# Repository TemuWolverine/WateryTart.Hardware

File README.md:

## [WateryTart.RaspberryPi](WateryTart.RaspberryPi/)

Raspberry Pi, a touchscreen, Hifiberry, to make a standalone amplifier/streamer that can power 30+30w speakers.
Includes 
* Fusion360 model, 
* build guide, 
* software options.

## [WateryTart.Remote](WateryTart.Remote) (work in progress)
ESP32/ESPHome based remote control to handle a household of Music Assistant devices. 

Includes
* YAML (ESPHome + HomeAssistant)
* KiCad files for custom PCB
* Gerber files for order custom PCB
* Fusion360 model

## WateryTart.Streamer (TBD)

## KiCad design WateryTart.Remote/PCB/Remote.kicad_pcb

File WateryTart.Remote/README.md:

# WateryTart.Remote
A work in progress custom remote aimed at Music Assistant devices.

## [Interactive Schematic](https://kicanvas.org/?repo=https%3A%2F%2Fgithub.com%2FTemuWolverine%2FWateryTart.Hardware%2Fblob%2Fmain%2FWateryTart.Remote%2FPCB%2FRemote.kicad_sch)
## [Interactive PCB layout](https://kicanvas.org/?repo=https%3A%2F%2Fgithub.com%2FTemuWolverine%2FWateryTart.Hardware%2Fblob%2Fmain%2FWateryTart.Remote%2FPCB%2FRemote.kicad_pcb)

## Proposed Parts List
(Links to follow eventually)
* Wemos Lolin D32 (MCU)
* ssd1306 i2c (Display)
* 0.1 uF capacitor
* SW-200D tilt switch
* 12 6x6x6 push buttons
* lipo battery

Mech parts
* 3x M2.5? M3? heat set inserts & screws

Everything will be hand solderable

### Rendering of PCB

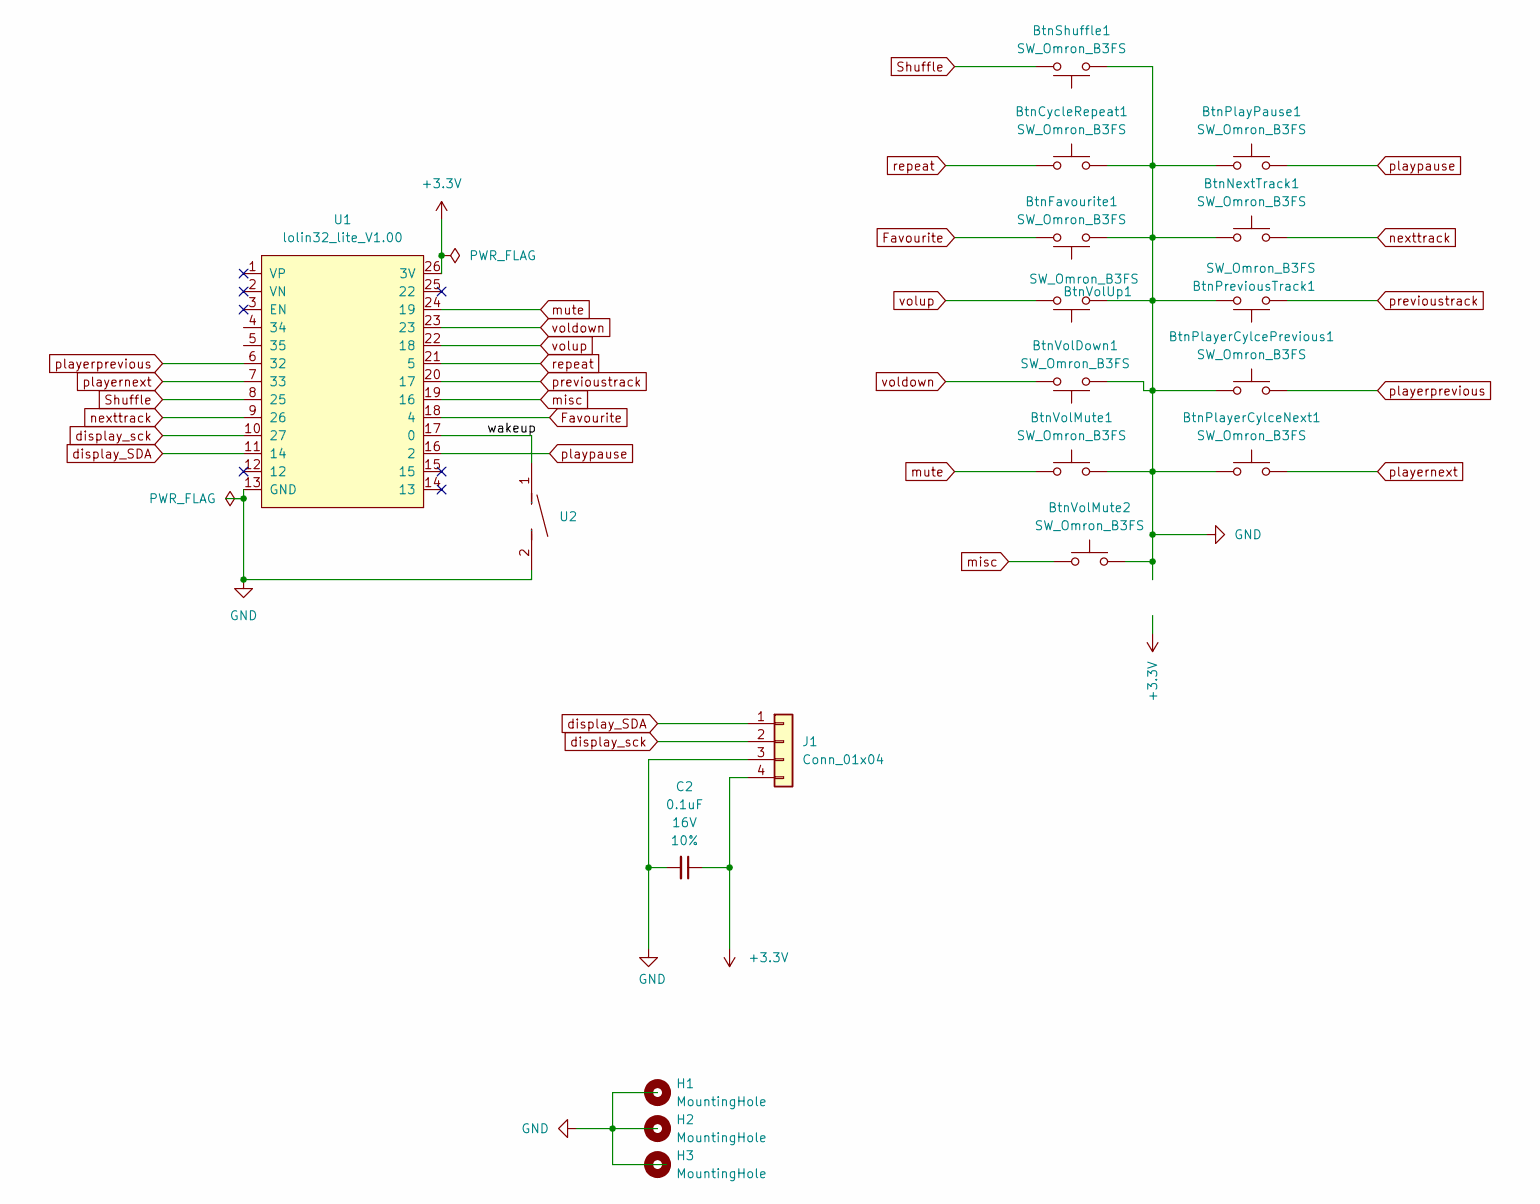
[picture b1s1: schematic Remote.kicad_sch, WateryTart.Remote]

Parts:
BtnCycleRepeat1: SW_Omron_B3FS; SW_PUSH_6mm_H5mm
BtnFavourite1: SW_Omron_B3FS; SW_PUSH_6mm_H5mm
BtnNextTrack1: SW_Omron_B3FS; SW_PUSH_6mm_H5mm
BtnPlayPause1: SW_Omron_B3FS; SW_PUSH_6mm_H5mm
BtnPlayerCylceNext1: SW_Omron_B3FS; SW_PUSH_6mm_H5mm
BtnPlayerCylcePrevious1: SW_Omron_B3FS; SW_PUSH_6mm_H5mm
BtnPreviousTrack1: SW_Omron_B3FS; SW_PUSH_6mm_H5mm
BtnShuffle1: SW_Omron_B3FS; SW_PUSH_6mm_H5mm
BtnVolDown1: SW_Omron_B3FS; SW_PUSH_6mm_H5mm
BtnVolMute1, BtnVolMute2: SW_Omron_B3FS; SW_PUSH_6mm_H5mm
BtnVolUp1: SW_Omron_B3FS; SW_PUSH_6mm_H5mm
C2: 0.1uF; C_Disc_D5.0mm_W2.5mm_P5.00mm; Voltage 16V; Tolerance 10%
H1, H2, H3: MountingHole; MountingHole_3.2mm_M3_Pad
J1: Conn_01x04; PinSocket_1x04_P2.54mm_Vertical
U1: lolin32_lite_V1.00; WEMOS_LOLIN32_LITE
U2: SW-TH_BD3.6-L10.6-LS12.6-D0.4; Manufacturer Part SW-200D 053; LCSC Part Name SW-200D双珠

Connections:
+3.3V: C2.1, J1.4, U1.26 (3V)
/wakeup: U1.17 (0), U2.1
Favourite: BtnFavourite1.2, U1.18 (4)
GND: BtnCycleRepeat1.2, BtnFavourite1.1, BtnNextTrack1.1, BtnPlayPause1.1, BtnPlayerCylceNext1.1, BtnPlayerCylcePrevious1.1, BtnPreviousTrack1.2, BtnShuffle1.1, BtnVolDown1.1, BtnVolMute1.2, BtnVolMute2.2, BtnVolUp1.1, C2.2, J1.3, U1.13 (GND), U2.2
Shuffle: BtnShuffle1.2, U1.8 (25)
display_SDA: J1.1, U1.11 (14)
display_sck: J1.2, U1.10 (27)
misc: BtnVolMute2.1, U1.19 (16)
mute: BtnVolMute1.1, U1.24 (19)
nexttrack: BtnNextTrack1.2, U1.9 (26)
playernext: BtnPlayerCylceNext1.2, U1.7 (33)
playerprevious: BtnPlayerCylcePrevious1.2, U1.6 (32)
playpause: BtnPlayPause1.2, U1.16 (2)
previoustrack: BtnPreviousTrack1.1, U1.20 (17)
repeat: BtnCycleRepeat1.1, U1.21 (5)
voldown: BtnVolDown1.2, U1.23
volup: BtnVolUp1.2, U1.22 (18)

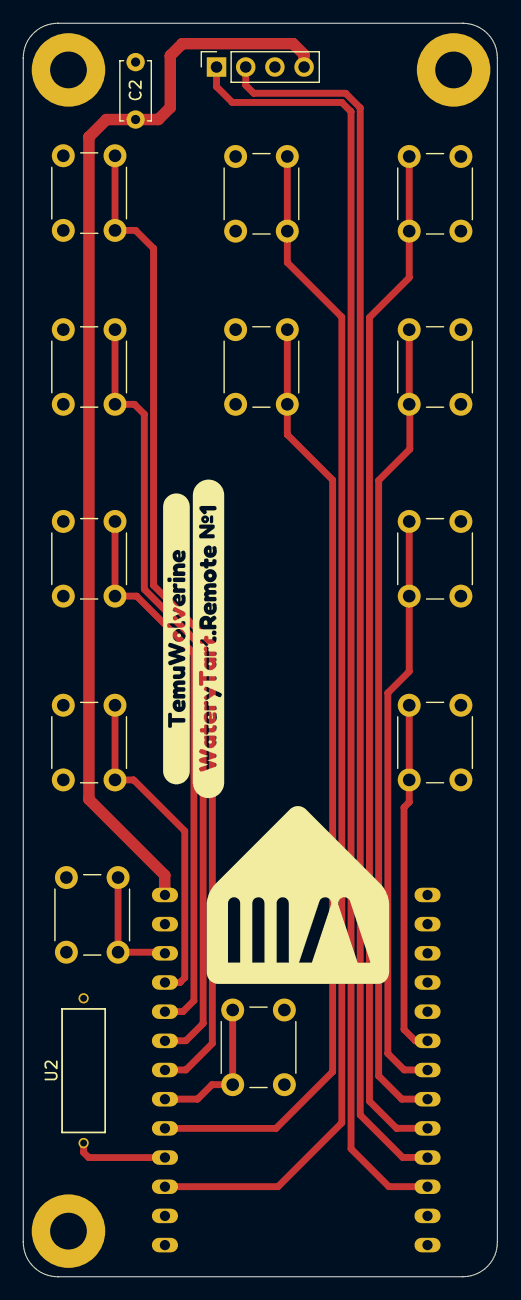
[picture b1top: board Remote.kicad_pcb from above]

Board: 2 copper layers, 41.3 x 109.1 mm, 21 parts (1 on the bottom side), 17 nets.

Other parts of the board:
kibuzzard-69A777E0: G***; kibuzzard-69A777E0
kibuzzard-69A777EC: G***; kibuzzard-69A777EC

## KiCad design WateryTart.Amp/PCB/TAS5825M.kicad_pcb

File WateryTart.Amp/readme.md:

Circuit design for a TAS5825M I2S amplifier.
Design is from [Jesse van der Zouw](https://e2e.ti.com/support/audio-group/audio/f/audio-forum/759036/tas5825m-free-tas5825m-breakout-board-design/), modified for easier mounting

I'd also consider using a TAS5828M chip - its physically larger and will dissipate heat better.

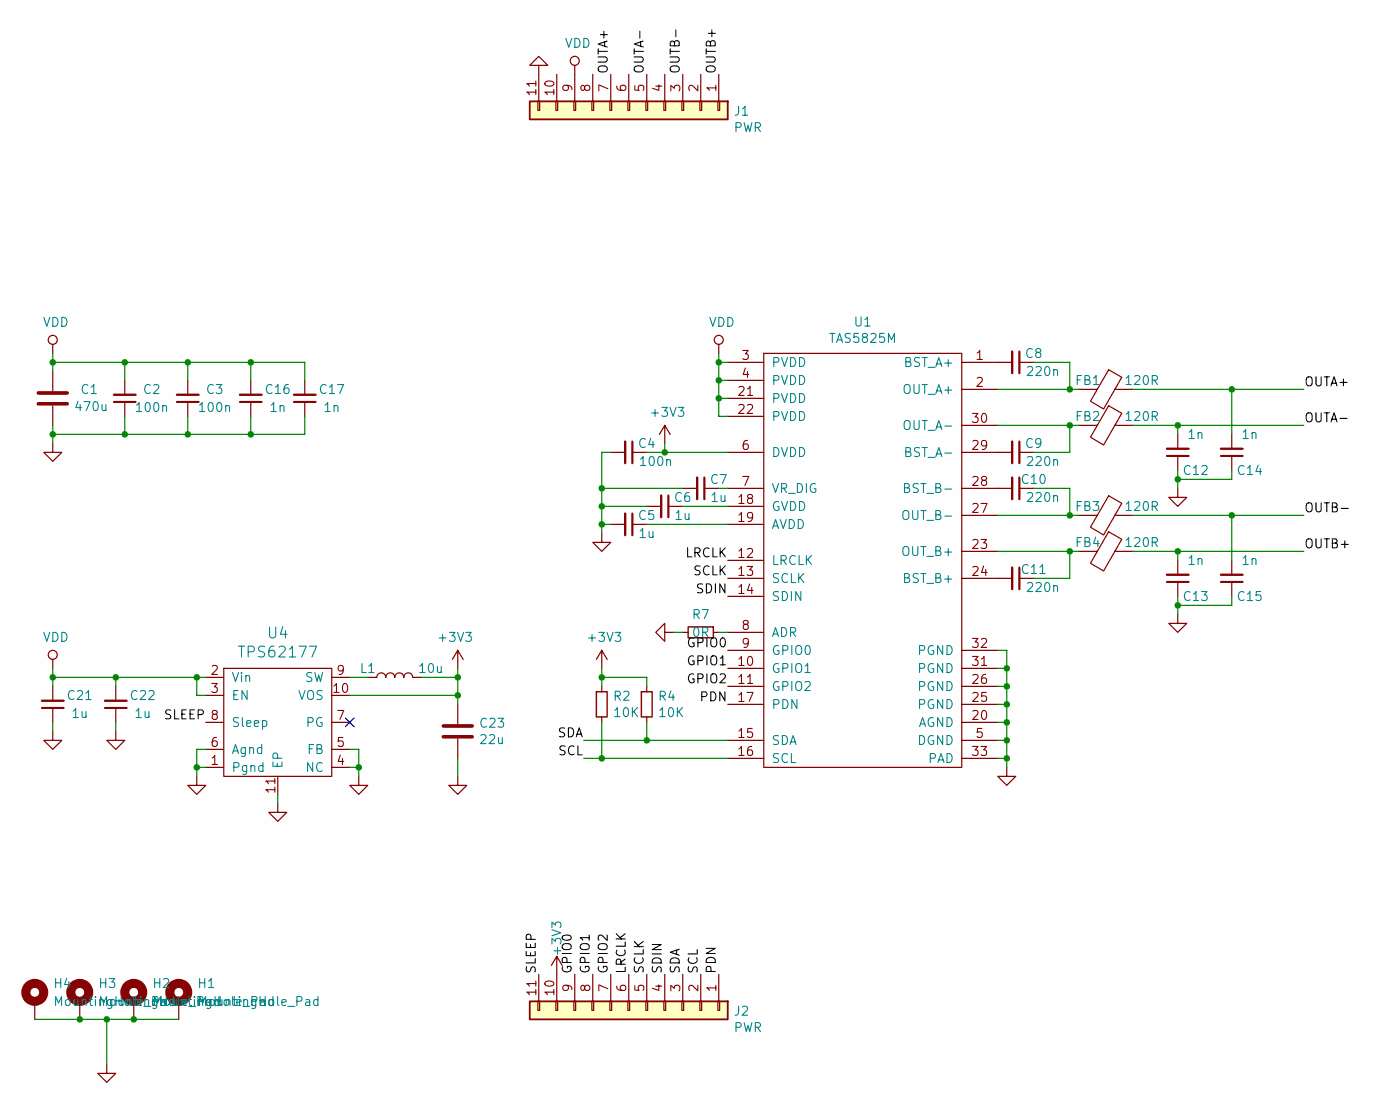
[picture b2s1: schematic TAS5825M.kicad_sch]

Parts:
C1: 470u; Cap_Rad_D10_P5
C2, C3, C4: 100n; C0603
C5, C6, C7, C21, C22: 1u; C0805
C8, C9, C10, C11: 220n; C0603
C12, C13, C14, C15, C16, C17: 1n; C0603
C23: 22u; C1210
FB1, FB2, FB3, FB4: 120R; C1206
H1, H2, H3, H4: MountingHole_Pad; MountingHole_2.5mm_Pad
J1, J2: PWR; PinHeader_1x11_P2.54mm_Vertical
L1: 10u; TYS4012100M
R2, R4: 10K; R0603
R7: 0R; R0603
U1: TAS5825M
U4: TPS62177; WSON10EP

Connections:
+3V3: C4.1, C23.1, J2.10, L1.2, R2.1, R4.1, U1.6 (DVDD), U4.10 (VOS)
/GPIO0: J2.9, U1.9 (GPIO0)
/GPIO1: J2.8, U1.10 (GPIO1)
/GPIO2: J2.7, U1.11 (GPIO2)
/LRCLK: J2.6, U1.12 (LRCLK)
/OUTA+: C14.2, FB1.1, J1.7
/OUTA-: C12.2, FB2.1, J1.5
/OUTB+: C13.2, FB4.1, J1.1
/OUTB-: C15.2, FB3.1, J1.3
/PDN: J2.1, U1.17 (PDN)
/SCL: J2.2, R2.2, U1.16 (SCL)
/SCLK: J2.5, U1.13 (SCLK)
/SDA: J2.3, R4.2, U1.15 (SDA)
/SDIN: J2.4, U1.14 (SDIN)
/SLEEP: J2.11, U4.8 (Sleep)
GND: C1.2, C2.1, C3.1, C4.2, C5.2, C6.2, C7.2, C12.1, C13.1, C14.1, C15.1, C16.1, C17.1, C21.1, C22.1, C23.2, H1.1, H2.1, H3.1, H4.1, J1.11, R7.2, U1.5 (DGND), U1.20 (AGND), U1.25 (PGND), U1.26 (PGND), U1.31 (PGND), U1.32 (PGND), U1.33 (PAD), U4.1 (Pgnd), U4.4 (NC), U4.5 (FB), U4.6 (Agnd), U4.11 (EP)
unnamed: R7.1, U1.8 (ADR)
unnamed: C5.1, U1.19 (AVDD)
unnamed: C8.2, U1.1 (BST_A+)
unnamed: C9.2, U1.29 (BST_A-)
unnamed: C11.2, U1.24 (BST_B+)
unnamed: C10.2, U1.28 (BST_B-)
unnamed: C6.1, U1.18 (GVDD)
unnamed: C8.1, FB1.2, U1.2 (OUT_A+)
unnamed: C9.1, FB2.2, U1.30 (OUT_A-)
unnamed: C11.1, FB4.2, U1.23 (OUT_B+)
unnamed: C10.1, FB3.2, U1.27 (OUT_B-)
unnamed: C7.1, U1.7 (VR_DIG)
unnamed: L1.1, U4.9 (SW)
VDD: C1.1, C2.2, C3.2, C16.2, C17.2, C21.2, C22.2, J1.9, U1.3 (PVDD), U1.4 (PVDD), U1.21 (PVDD), U1.22 (PVDD), U4.2 (Vin), U4.3 (EN)

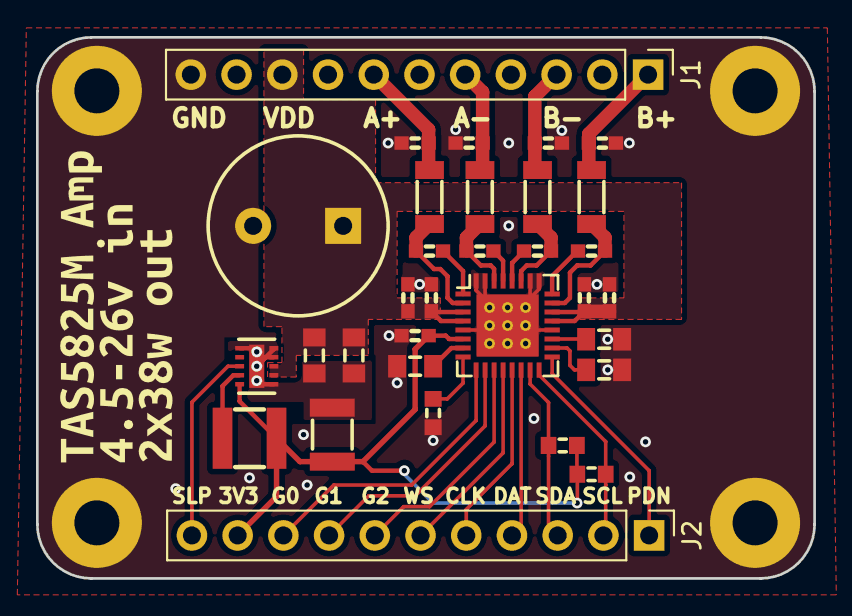
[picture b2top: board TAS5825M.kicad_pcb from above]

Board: 2 copper layers, 43.2 x 30.1 mm, 37 parts (0 on the bottom side), 30 nets.

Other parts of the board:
kibuzzard-69B532CA: G***; kibuzzard-69B532CA

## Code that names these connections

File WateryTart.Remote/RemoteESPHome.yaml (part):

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  pin_i2c_scl: GPIO27

  #Wakup switch
  pin_wakeup: GPIO0

  #Row 1
  pin_track_previous: GPIO17
  pin_play_pause: GPIO2
  pin_track_next: GPIO26

  #Row 2
  pin_repeat: GPIO5
  pin_fav: GPIO4
  pin_shuffle: GPIO25

  #Row 3
  pin_vol_up: GPIO18
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  
  #Row5
  pin_vol_mute: GPIO19
  pin_misc: GPIO16


  time_before_sleep: 60 #in seconds
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deep_sleep:
  id: deep_sleep_ctrl
  sleep_duration: 2800 min
  wakeup_pin:
    - pin:
        number: ${pin_wakeup}
        inverted: True  # will wake up when P8 is low
      wakeup_pin_mode: KEEP_AWAKE # will prevent sleep as long as P8 is low

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binary_sensor:
#  - platform: gpio
#    pin:
#      number: ${pin_wakeup}
#      inverted: True
#      mode:
#        input: true
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# Middle Row
  - platform: gpio
    pin:
        number: ${pin_repeat}
        mode:
          input: true
          pullup: true
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
  - platform: gpio
    pin:
        number: ${pin_shuffle}
        mode:
          input: true
          pullup: true
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

  #pin_fav: GPIO14 ##No such HA command
  #pin_repeat: GPIO21 #media_player.repeat_set off/all/one
  #pin_shuffle: GPIO32 #media_player.shuffle_set true/false

#Volume Rocker
  - platform: gpio
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
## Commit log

2026-03-05 merged hardware repos
2026-03-11 Added CYD
2026-03-14 Added initial amp pcb import
2026-03-21 stub code for JC4880P443
2026-04-05 Finalised schematic and pcb layout ready for first round of mfg
2026-04-05 added sleepytime stuff.
2026-04-30 init model
